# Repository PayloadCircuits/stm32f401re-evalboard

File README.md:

# STM32F401RE Evaluation Board
Two-layer STM32F401RE (LQFP64) evaluation board designed in KiCad, built as
a solo entry for the **Mixed Traces PCB Design Competition**, hosted by
Mixed Signals (Electronics Association of MEC).

# Overview
A compact, self-contained STM32F401RE dev board inspired by the
NUCLEO-F401RE reference design, built to fit within a 100mm x 100mm,
two-layer PCB. Per the competition rules, an on-board ST-LINK debugger is
not required — programming and debugging are handled through an external
SWD header instead.

## Features
- STM32F401RET6 (LQFP64) microcontroller
- USB-C power input with CC1/CC2 pull-downs and USBLC6-2SC6 ESD protection
- NCP1117-3.3 LDO regulation
- 8MHz HSE crystal (derives both the 84MHz system clock and 48MHz USB clock)
- External SWD header for programming/debugging
- UART, SPI, and I2C headers
- 34 GPIO broken out across four expansion headers, each with 3V3/GND
  reference pins
- Dedicated power breakout header (VBUS, 3V3, GND)
- User + reset buttons, user + power LEDs
- Full ground plane pour on both copper layers

# Tools
Designed entirely in [KiCad](https://www.kicad.org/) 9.

# Schematic
- https://github.com/PayloadCircuits/stm32f401re-evalboard/blob/main/Screenshot%202026-09-03%20185406.png
- https://github.com/PayloadCircuits/stm32f401re-evalboard/blob/main/schematic.pdf

# PCB Layout
https://github.com/PayloadCircuits/stm32f401re-evalboard/blob/main/Screenshot%202026-09-03%20184711.png

# Gerber
https://github.com/PayloadCircuits/stm32f401re-evalboard/blob/main/GERBER.zip

# Render Images
- https://github.com/PayloadCircuits/stm32f401re-evalboard/blob/main/Screenshot%202026-09-03%20185029.png
- https://github.com/PayloadCircuits/stm32f401re-evalboard/blob/main/Screenshot%202026-09-03%20185117.png
- https://github.com/PayloadCircuits/stm32f401re-evalboard/blob/main/Screenshot%202026-09-03%20185238.png

# BOM with estimated component cost
https://github.com/PayloadCircuits/stm32f401re-evalboard/blob/main/BOM%20estimate.pdf

# ERC and DRC results
- https://github.com/PayloadCircuits/stm32f401re-evalboard/blob/main/Screenshot%202026-09-15%20185338.png
- https://github.com/PayloadCircuits/stm32f401re-evalboard/blob/main/Screenshot%202026-09-15%20185429.png

# Status
Entered in the Mixed Traces PCB Design Competition — progress checkpoint
submitted 5 September 2026, final submission due 15 September 2026.

# License
Hardware design files in this repository are licensed under the
[CERN Open Hardware Licence Version 2 - Permissive (CERN-OHL-P-2.0)](LICENSE).

# Author
Adarsh S — [Payload Circuits](https://github.com/PayloadCircuits)

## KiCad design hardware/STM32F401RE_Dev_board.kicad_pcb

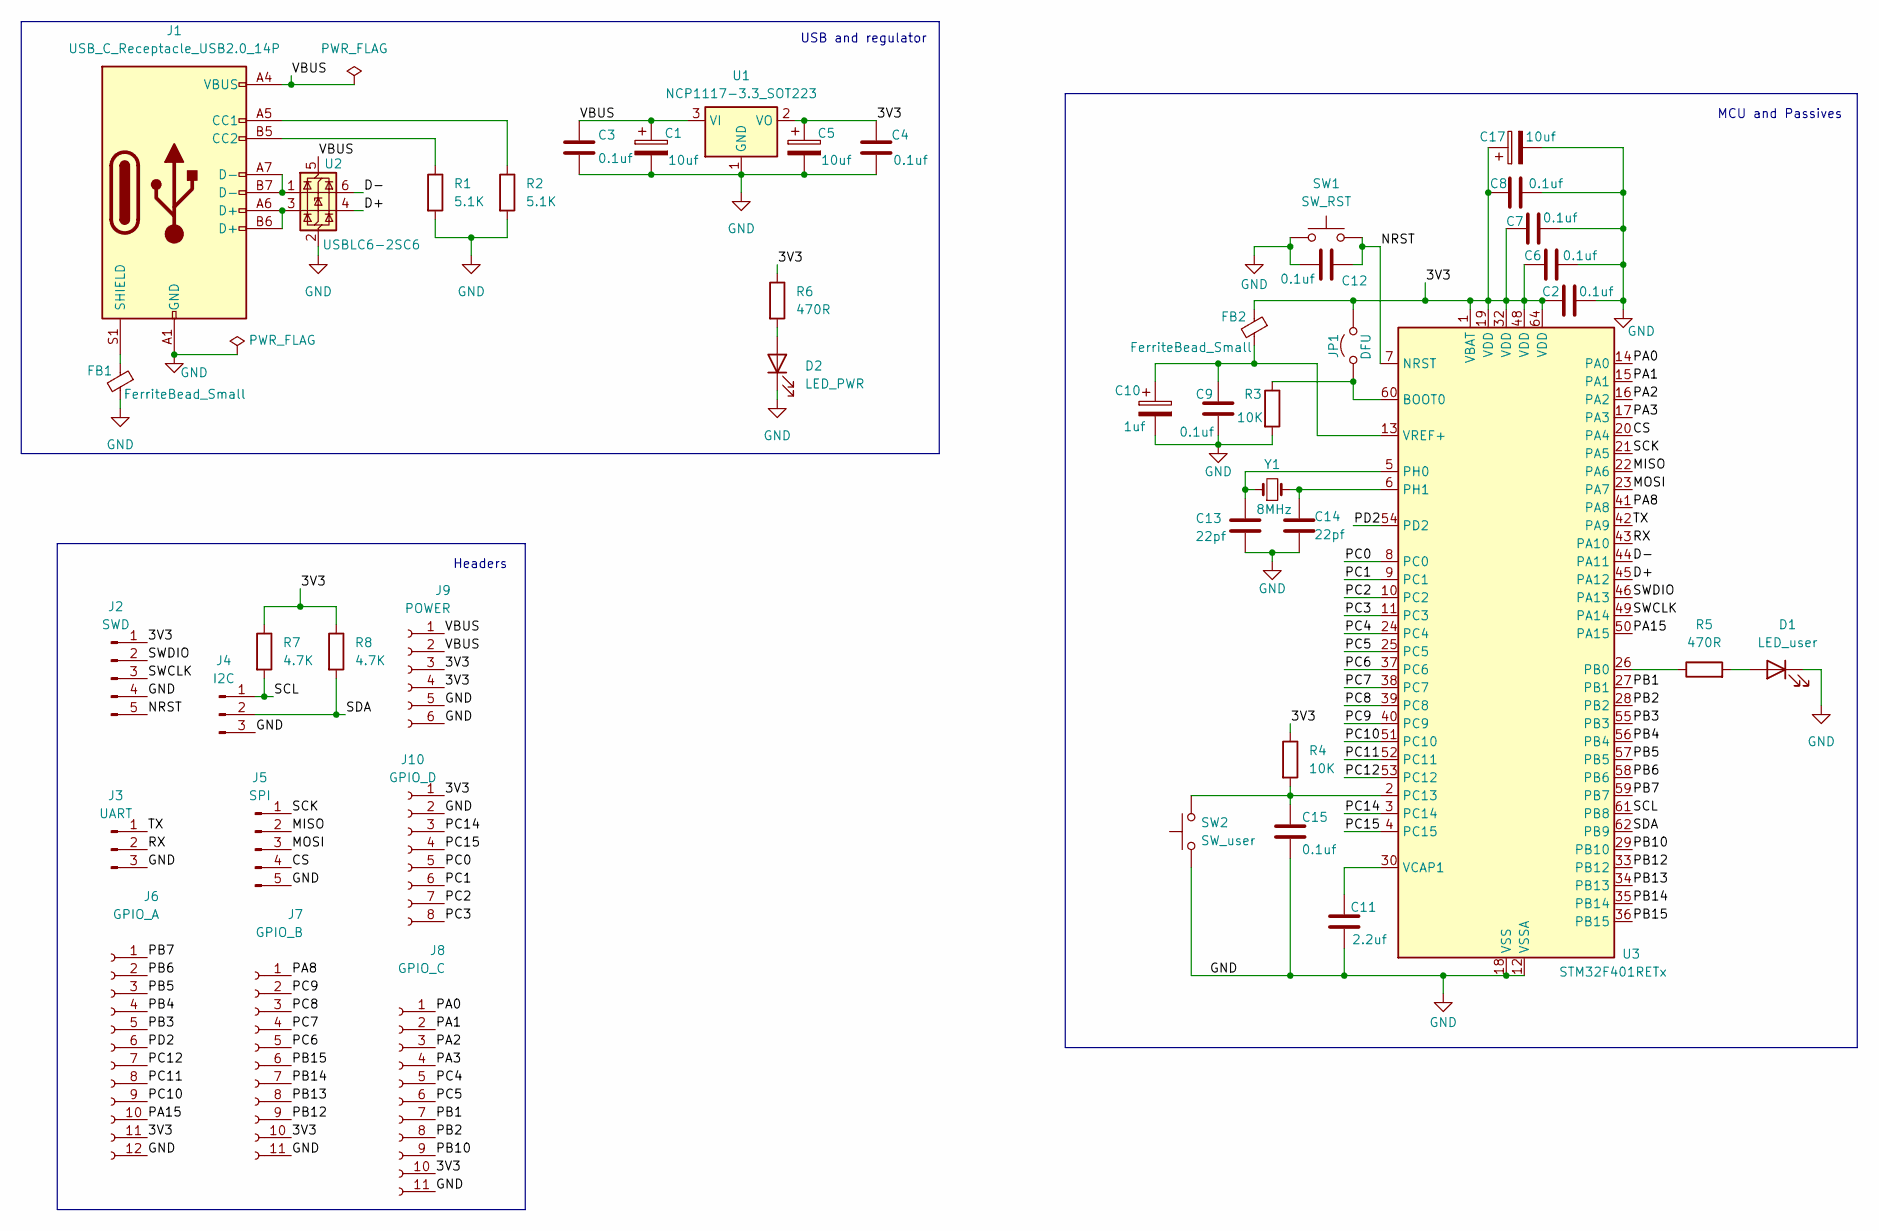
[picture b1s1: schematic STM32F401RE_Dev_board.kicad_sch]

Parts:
C1, C5, C17: 10uf; C_0805_2012Metric_Pad1.18x1.45mm_HandSolder
C2, C3, C4, C6, C7, C8, C9, C12, C15: 0.1uf; C_0201_0603Metric_Pad0.64x0.40mm_HandSolder
C10: 1uf; C_0805_2012Metric_Pad1.18x1.45mm_HandSolder
C11: 2.2uf; C_0805_2012Metric_Pad1.18x1.45mm_HandSolder
C13, C14: 22pf; C_0201_0603Metric_Pad0.64x0.40mm_HandSolder
D1: LED_user; LED_0805_2012Metric_Pad1.15x1.40mm_HandSolder
D2: LED_PWR; LED_0805_2012Metric_Pad1.15x1.40mm_HandSolder
FB1, FB2: FerriteBead_Small; L_0603_1608Metric_Pad1.05x0.95mm_HandSolder
J1: USB_C_Receptacle_USB2.0_14P; USB_C_Receptacle_GCT_USB4085
J2: SWD; PinHeader_1x05_P2.54mm_Vertical
J3: UART; PinHeader_1x03_P2.54mm_Vertical
J4: I2C; PinHeader_1x03_P2.54mm_Vertical
J5: SPI; PinHeader_1x05_P2.54mm_Vertical
J6: GPIO_A; PinSocket_1x12_P2.54mm_Vertical
J7: GPIO_B; PinSocket_1x11_P2.54mm_Vertical
J8: GPIO_C; PinSocket_1x11_P2.54mm_Vertical
J9: POWER; PinSocket_1x06_P2.54mm_Vertical
J10: GPIO_D; PinSocket_1x08_P2.54mm_Vertical
JP1: DFU; PinHeader_1x02_P2.54mm_Vertical
R1, R2: 5.1K; R_0201_0603Metric_Pad0.64x0.40mm_HandSolder
R3, R4: 10K; R_0201_0603Metric_Pad0.64x0.40mm_HandSolder
R5, R6: 470R; R_0201_0603Metric_Pad0.64x0.40mm_HandSolder
R7, R8: 4.7K; R_0201_0603Metric_Pad0.64x0.40mm_HandSolder
SW1: SW_RST; SW_SPST_TL3342
SW2: SW_user; SW_SPST_TL3342
U1: NCP1117-3.3_SOT223; SOT-223-3_TabPin2
U2: USBLC6-2SC6; SOT-23-6
U3: STM32F401RETx; LQFP-64_10x10mm_P0.5mm
Y1: 8MHz; Crystal_SMD_0603-2Pin_6.0x3.5mm_HandSoldering

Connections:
/3V3: C2.1, C4.1, C5.1, C6.1, C7.1, C8.1, C17.1, FB2.1, J2.1, J6.11, J7.10, J8.10, J9.3, J9.4, J10.1, JP1.2 (B), R4.1, R6.1, R7.1, R8.1, U1.2 (VO), U3.1 (VBAT), U3.19 (VDD), U3.32 (VDD), U3.48 (VDD), U3.64 (VDD)
/CS: J5.4, U3.20 (PA4)
/D+: U2.4 (I/O2), U3.45 (PA12)
/D-: U2.6 (I/O1), U3.44 (PA11)
/MISO: J5.2, U3.22 (PA6)
/MOSI: J5.3, U3.23 (PA7)
/NRST: C12.1, J2.5, SW1.2, U3.7 (NRST)
/PA0: J8.1, U3.14 (PA0)
/PA1: J8.2, U3.15 (PA1)
/PA2: J8.3, U3.16 (PA2)
/PA3: J8.4, U3.17 (PA3)
/PA8: J7.1, U3.41 (PA8)
/PA15: J6.10, U3.50 (PA15)
/PB1: J8.7, U3.27 (PB1)
/PB2: J8.8, U3.28 (PB2)
/PB3: J6.5, U3.55 (PB3)
/PB4: J6.4, U3.56 (PB4)
/PB5: J6.3, U3.57 (PB5)
/PB6: J6.2, U3.58 (PB6)
/PB7: J6.1, U3.59 (PB7)
/PB10: J8.9, U3.29 (PB10)
/PB12: J7.9, U3.33 (PB12)
/PB13: J7.8, U3.34 (PB13)
/PB14: J7.7, U3.35 (PB14)
/PB15: J7.6, U3.36 (PB15)
/PC0: J10.5, U3.8 (PC0)
/PC1: J10.6, U3.9 (PC1)
/PC2: J10.7, U3.10 (PC2)
/PC3: J10.8, U3.11 (PC3)
/PC4: J8.5, U3.24 (PC4)
/PC5: J8.6, U3.25 (PC5)
/PC6: J7.5, U3.37 (PC6)
/PC7: J7.4, U3.38 (PC7)
/PC8: J7.3, U3.39 (PC8)
/PC9: J7.2, U3.40 (PC9)
/PC10: J6.9, U3.51 (PC10)
/PC11: J6.8, U3.52 (PC11)
/PC12: J6.7, U3.53 (PC12)
/PC14: J10.3, U3.3 (PC14)
/PC15: J10.4, U3.4 (PC15)
/PD2: J6.6, U3.54 (PD2)
/RX: J3.2, U3.43 (PA10)
/SCK: J5.1, U3.21 (PA5)
/SCL: J4.1, R7.2, U3.61 (PB8)
/SDA: J4.2, R8.2, U3.62 (PB9)
/SWCLK: J2.3, U3.49 (PA14)
/SWDIO: J2.2, U3.46 (PA13)
/TX: J3.1, U3.42 (PA9)
/VBUS: C1.1, C3.1, J1.A4 (VBUS), J1.A9 (VBUS), J1.B4 (VBUS), J1.B9 (VBUS), J9.1, J9.2, U1.3 (VI), U2.5 (VBUS)
GND: C1.2, C2.2, C3.2, C4.2, C5.2, C6.2, C7.2, C8.2, C9.2, C10.2, C11.2, C12.2, C13.2, C14.2, C15.2, C17.2, D1.1 (K), D2.1 (K), FB1.2, J1.A1 (GND), J1.A12 (GND), J1.B1 (GND), J1.B12 (GND), J2.4, J3.3, J4.3, J5.5, J6.12, J7.11, J8.11, J9.5, J9.6, J10.2, R1.2, R2.2, R3.2, SW1.1, SW2.1, U1.1 (GND), U2.2 (GND), U3.12 (VSSA), U3.18 (VSS), U3.31 (VSS), U3.47 (VSS), U3.63 (VSS)
unnamed: D1.2 (A), R5.2
unnamed: D2.2 (A), R6.2
unnamed: J1.A5 (CC1), R2.1
unnamed: J1.B5 (CC2), R1.1
unnamed: J1.A6 (D+), J1.B6 (D+), U2.3 (I/O2)
unnamed: J1.A7 (D-), J1.B7 (D-), U2.1 (I/O1)
unnamed: FB1.1, J1.S1 (SHIELD)
unnamed: JP1.1 (A), R3.1, U3.60 (BOOT0)
unnamed: R5.1, U3.26 (PB0)
unnamed: C15.1, R4.2, SW2.2, U3.2 (PC13)
unnamed: C13.1, U3.5 (PH0), Y1.1
unnamed: C14.1, U3.6 (PH1), Y1.2
unnamed: C11.1, U3.30 (VCAP1)
unnamed: C9.1, C10.1, FB2.2, U3.13 (VREF+)

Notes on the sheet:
Headers
USB and regulator
MCU and Passives

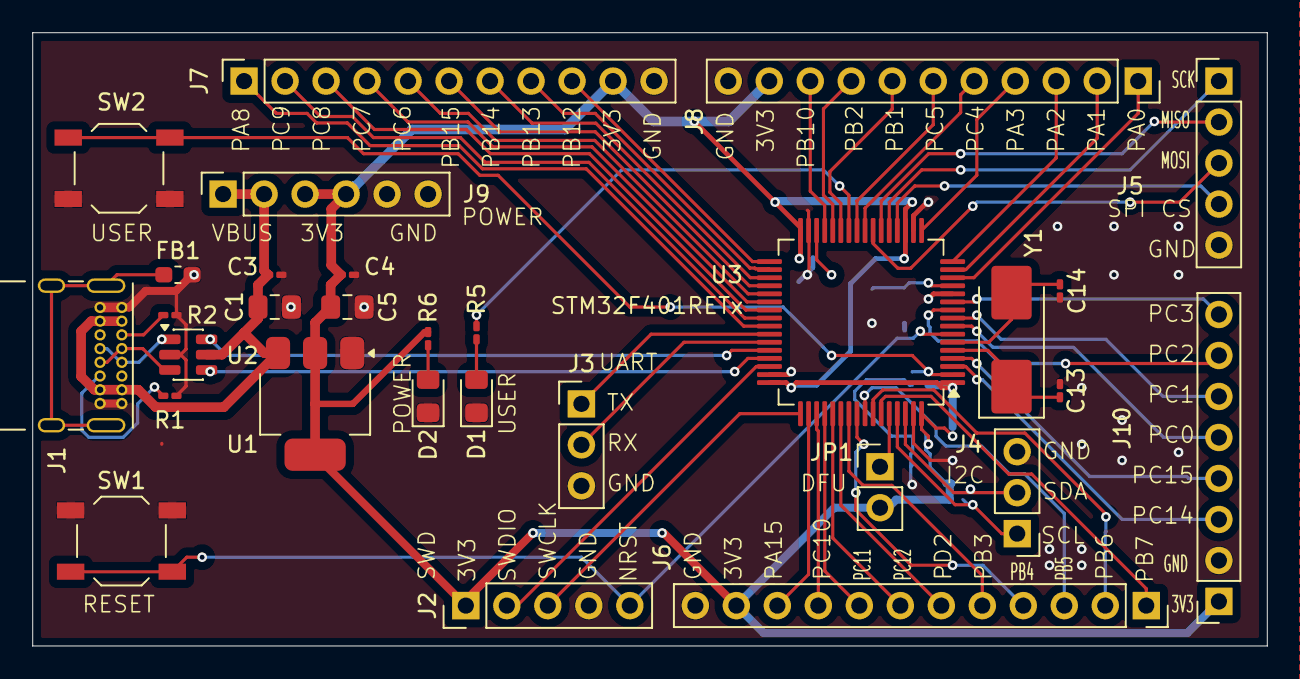
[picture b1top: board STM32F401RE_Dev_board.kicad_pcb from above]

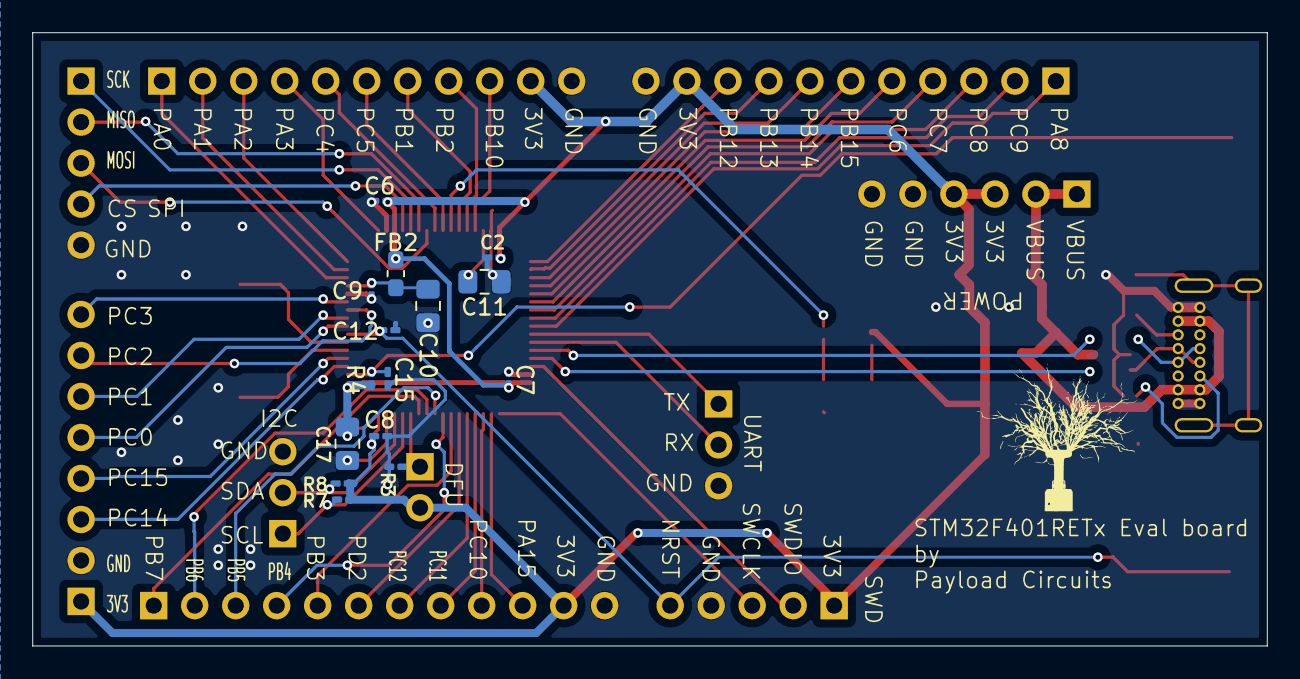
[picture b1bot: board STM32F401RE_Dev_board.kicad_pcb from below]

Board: 2 copper layers, 76.5 x 38.0 mm, 45 parts (15 on the bottom side), 64 nets.
